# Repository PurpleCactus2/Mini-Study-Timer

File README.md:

# Mini-Study-Timer
A small and portable study timer for keeping track of the time you spend learning or working on projects!

## Introduction
This is a mini study timer meant to track the time that you have spent studying. Its features include:

- A 0.91" OLED display to display the timer
- Buttons to control start/stop/pause/reset
- Visual indicator LEDs
- Planned functionality with a rotary encoder to set time

## PCB
My aim with the PCB was to make it relatively compact so that you could easily fit it into a backpack or pocket. But at the same time I also wanted to make it easy to work with since I am quite inexperienced with soldering and assembly.

### Schematic
The schematic itself follows a pretty regular layout.

Here is the XIAO ESP32 C3 as the main microcontroller:
<br>

The battery will connect to the battery pads on the bottom of the Xiao (*see PCB*)<br><br>

Here is the 0.91" OLED:
<br><br>

I have included some extra pullup resistors and decoupling capacitors as recommended by the guide.<br><br>

This is the rotary encoder:
<br><br>

I have included a very basic filter to hopefully help with debouncing.<br><br>

Here are the rest of the components:
<br>

These are the basic switches, LEDs and extra I2C headers that I have included along with a JST-PH connector for the battery.<br><br>

### PCB
As I said before, I have tried compacting the PCB layout quite a bit:
<br>

But I have also tried to arrange the parts in a way that makes sense, with the buttons and encoder below the screen and with the power switch on the right.<br><br>

Here are those battery pads I was talking about within the footprint of the Xiao:
<br><br>

To connect these pads to the PCB I will simply push a header pin through the hole from the other side and solder it that way.

## Code
At its core the code runs a basic timer with the buttons controlling its main functions.
Here is a table showing the controls and functions of the timer:

| Component | Function |
|---|---|
| SW1 (Left on PCB) | Starts/pauses timer |
| SW2 (Right on PCB) | Resets and stops the timer |
| Rotary Encoder (UNFINISHED FEATURE) | Sets a countdown timer |
| Red LED | Lights up when timer is stopped |
| Green LED | Lights up when timer is active |

Unfortunately I was unable to completely finish the code for the rotary encoder in time, so right now the device can only count up the minutes and hours you have spent working.

[Here](https://wokwi.com/projects/479273044321545217) is the simulation i've made on WokWi to test the current functions (Note: I have absolutely no idea why, but the green LED connected to D6 on the XIAO ESP32 C3 simply refuses to turn on)

## BOM
|Item                    |Qty|Supplier  |Cost/item|Total Cost|link                                                                                                                                                                                                                                                                                                                                                                                                                                                                                                                                                                                                                                                                                                                                                                                    |
|------------------------|---|----------|---------|----------|----------------------------------------------------------------------------------------------------------------------------------------------------------------------------------------------------------------------------------------------------------------------------------------------------------------------------------------------------------------------------------------------------------------------------------------------------------------------------------------------------------------------------------------------------------------------------------------------------------------------------------------------------------------------------------------------------------------------------------------------------------------------------------------|
|XIAO ESP32 C3           |1  |AliExpress|$8.55    |$8.55     |[AliExpress](https://www.aliexpress.com/item/1005008791937363.html?spm=a2g0o.productlist.main.2.3fccf128mRG5wj&algo_pvid=f91a3f44-7054-4a6c-b5ca-71a791d5faf8&algo_exp_id=f91a3f44-7054-4a6c-b5ca-71a791d5faf8-1&pdp_ext_f=%7B%22order%22%3A%221602%22%2C%22eval%22%3A%221%22%2C%22fromPage%22%3A%22search%22%7D&pdp_npi=6%40dis%21NOK%2179.84%2111.94%21%21%218.33%211.25%21%400b5e1a3817935633084165522e0e0a%2112000052930246748%21sea%21NO%218463637778%21X%211%210%21n_tag%3A-29911%3Bd%3A22d43e35%3Bm03_new_user%3A-29895%3BpisId%3A5000000219877342&curPageLogUid=niJ9W14AGW5V&utparam-url=scene%3Asearch%7Cquery_from%3A%7Cx_object_id%3A1005008791937363%7C_p_origin_prod%3A)                                                                                                                 |
|0.91" OLED              |1  |AliExpress|$2.43    |$2.43     |[AliExpress](https://www.aliexpress.com/item/1005006823025817.html?spm=a2g0o.productlist.main.4.468b411fr6AAZN&algo_pvid=2569d209-d20a-4ce9-8cd6-a8dd480e45cc&aem_p4p_detail=20261101120438123246892630680005280555&algo_exp_id=2569d209-d20a-4ce9-8cd6-a8dd480e45cc-3&pdp_ext_f=%7B%22order%22%3A%22598%22%2C%22eval%22%3A%221%22%2C%22fromPage%22%3A%22search%22%7D&pdp_npi=6%40dis%21NOK%2122.67%2120.23%21%21%2115.69%2114.00%21%40210382de17935634779592233e10aa%2112000038417220460%21sea%21NO%218463637778%21X%211%210%21n_tag%3A-29911%3Bd%3A22d43e35%3Bm03_new_user%3A-29895%3BpisId%3A5000000220744683&curPageLogUid=QDjpxSoLt2EF&utparam-url=scene%3Asearch%7Cquery_from%3A%7Cx_object_id%3A1005006823025817%7C_p_origin_prod%3A&search_p4p_id=20261101120438123246892630680005280555_1)   |
|Rotary Encoder          |1  |AliExpress|$1.56    |$1.56     |[AliExpress](https://www.aliexpress.com/item/1005007644083514.html?spm=a2g0o.productlist.main.1.363968b6NvMQQN&algo_pvid=ecab3b09-9889-40fe-b5bb-468045627bf3&algo_exp_id=ecab3b09-9889-40fe-b5bb-468045627bf3-0&pdp_ext_f=%7B%22order%22%3A%224885%22%2C%22spu_best_type%22%3A%22price%22%2C%22eval%22%3A%221%22%2C%22fromPage%22%3A%22search%22%7D&pdp_npi=6%40dis%21NOK%2114.57%2110.45%21%21%211.52%211.10%21%400b88ab6717935636427541071e0f7b%2112000041630839409%21sea%21NO%218463637778%21X%211%210%21n_tag%3A-29911%3Bd%3A22d43e35%3Bm03_new_user%3A-29895%3BpisId%3A5000000219877342&curPageLogUid=OE90QjaOwzU0&utparam-url=scene%3Asearch%7Cquery_from%3A%7Cx_object_id%3A1005007644083514%7C_p_origin_prod%3A)                                                                             |
|Passive Components      |1  |AliExpress|$8.92    |$8.92     |[Capacitors](https://www.aliexpress.com/item/1005011747293156.html?spm=a2g0o.productlist.main.4.71c07baeewHVSt&algo_pvid=53fa7523-91ab-4fc5-9a37-791a7be0863d&aem_p4p_detail=202611011216112607374392124900005273353&algo_exp_id=53fa7523-91ab-4fc5-9a37-791a7be0863d-3&pdp_ext_f=%7B%22order%22%3A%223213%22%2C%22eval%22%3A%221%22%2C%22fromPage%22%3A%22search%22%7D&pdp_npi=6%40dis%21NOK%2122.06%2118.62%21%21%2115.27%2112.89%21%4021613ab217935641713446056e0fa2%2112000056423315138%21sea%21NO%218463637778%21X%211%210%21n_tag%3A-29911%3Bd%3A22d43e35%3Bm03_new_user%3A-29895%3BpisId%3A5000000221000707&curPageLogUid=9U2JRaZ3bgVG&utparam-url=scene%3Asearch%7Cquery_from%3A%7Cx_object_id%3A1005011747293156%7C_p_origin_prod%3A&search_p4p_id=202611011216112607374392124900005273353_3) [Resistors](https://www.aliexpress.com/item/1005002994755806.html?spm=a2g0o.cart.0.0.3f3a38dakuPmuS&mp=1&pdp_npi=6%40dis%21NOK%21NOK+29.90%21NOK+24.36%21%21NOK+24.36%21%21%21%400b8848e317935654396147496e0f29%2112000023122336560%21ct%21NO%218463637778%21%211%210%21)|
|JST-PH Connector        |1  |AliExpress|$1.67    |$1.67     |[AliExpress](https://www.aliexpress.com/item/1005004955655144.html?spm=a2g0o.productlist.main.33.673e3206X0j96K&algo_pvid=20e9831a-0538-42f5-89b6-7565b2dfc96a&algo_exp_id=20e9831a-0538-42f5-89b6-7565b2dfc96a-32&pdp_ext_f=%7B%22order%22%3A%223896%22%2C%22spu_best_type%22%3A%22price%22%2C%22eval%22%3A%221%22%2C%22fromPage%22%3A%22search%22%7D&pdp_npi=6%40dis%21NOK%218.34%216.96%21%21%210.87%210.73%21%400b88ab8a17935646038367827e104c%2112000033370425480%21sea%21NO%218463637778%21X%211%210%21n_tag%3A-29911%3Bd%3A22d43e35%3Bm03_new_user%3A-29895%3BpisId%3A5000000220732436&curPageLogUid=yGrFZekc6acZ&utparam-url=scene%3Asearch%7Cquery_from%3A%7Cx_object_id%3A1005004955655144%7C_p_origin_prod%3A)                                                                             |
|PCB                     |1  |JLCPCB    |$6.72    |$6.72     |[JLCPCB](https://cart.jlcpcb.com/quote?spm=jlcpcb.Public.2006&spm=Jlcpcb.Instantquote&spm=Jlcpcb.Instantquote&_t=1791669462672&_t=1793564789078&up_spm=Jlcpcb.Loginpage.1003&up_spm=Jlcpcb.Loginpage.1003)                                                                                                                                                                                                                                                                                                                                                                                                                                                                                                                                                                                        |
|3.7V LiPo               |1  |AliExpress|$4.11    |$4.11     |[AliExpress](https://www.aliexpress.com/item/1005010132479554.html?spm=a2g0o.productlist.main.1.401e5072TdpAZM&algo_pvid=f599faf2-6e03-4dbc-bcfc-387a4df46eb1&algo_exp_id=f599faf2-6e03-4dbc-bcfc-387a4df46eb1-0&pdp_ext_f=%7B%22order%22%3A%221236%22%2C%22spu_best_type%22%3A%22price%22%2C%22eval%22%3A%221%22%2C%22fromPage%22%3A%22search%22%7D&pdp_npi=6%40dis%21NOK%21217.91%2138.38%21%21%21150.81%2126.56%21%4021038b2f17935651508853358e0d64%2112000051255130084%21sea%21NO%218463637778%21X%211%210%21n_tag%3A-29911%3Bd%3A22d43e35%3Bm03_new_user%3A-29895%3BpisId%3A5000000219877342&curPageLogUid=Mbz1Z1oNIHlF&utparam-url=scene%3Asearch%7Cquery_from%3A%7Cx_object_id%3A1005010132479554%7C_p_origin_prod%3A)                                                                         |
|Estimated total shipping|1  |          |         |$5.86     |                                                                                                                                                                                                                                                                                                                                                                                                                                                                                                                                                                                                                                                                                                                                                                                        |

- The prices listed here represent the **maximum possible** prices for each of the items, in reality, significant discounts do apply
- I am completely willing to cover all additional costs that are not coverered by the base 30$

Cart Screenshots (1kr ≈ $0.1):

Aliexpress order:

Total (discounts at time checked + shipping/tax): **$29.22** <br> <br>

JLCPCB order:

Total (with discounts at time checked + shipping/tax): **$6.72**

Grand Total: **$35.94**

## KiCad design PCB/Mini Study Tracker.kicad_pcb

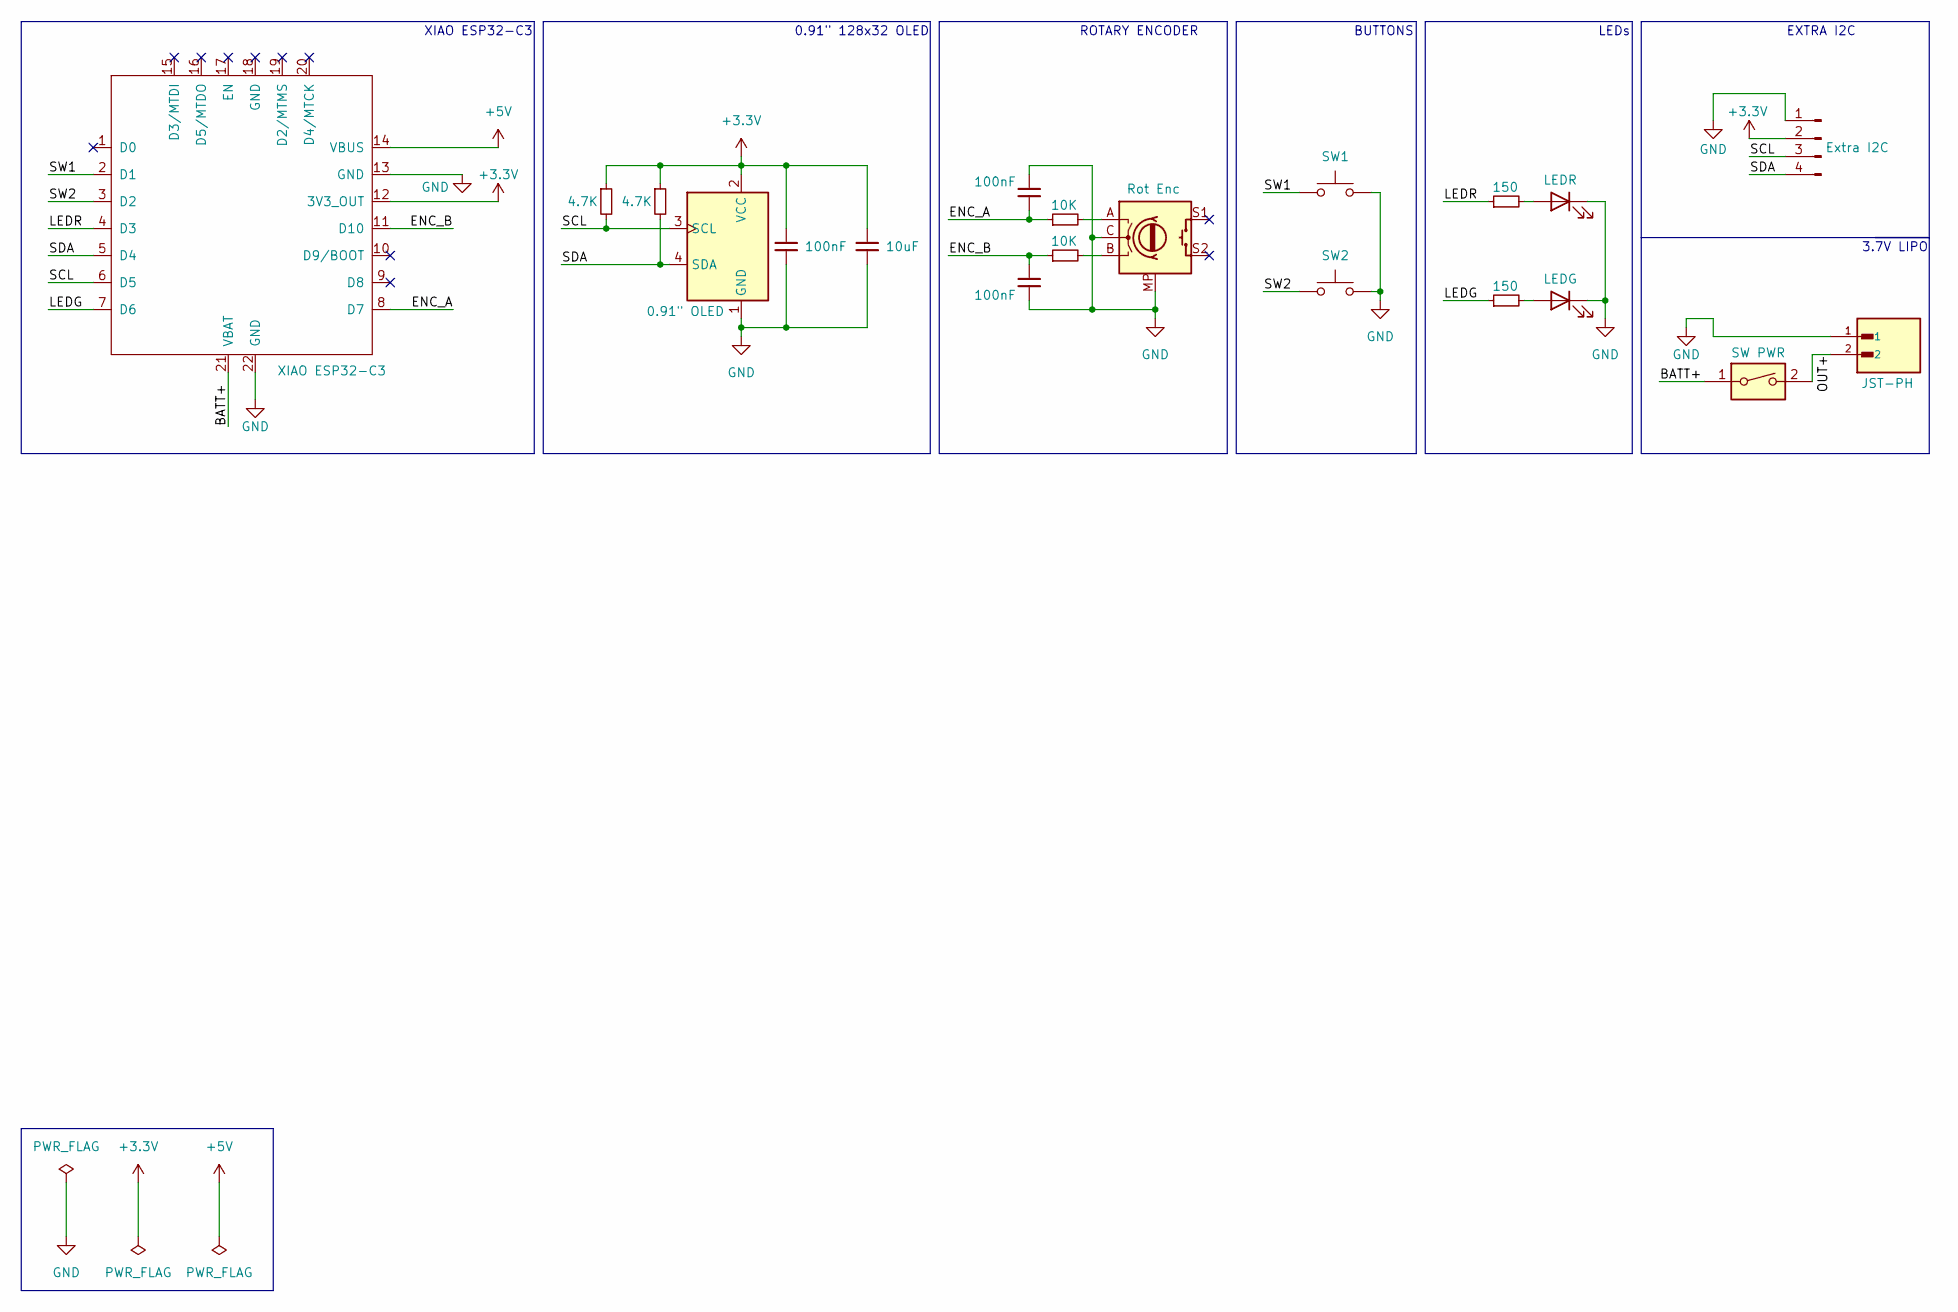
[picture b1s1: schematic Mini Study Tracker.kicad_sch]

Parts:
C1, C3, C4: 100nF; C_Disc_D4.7mm_W2.5mm_P5.00mm
C2: 10uF; C_Disc_D4.7mm_W2.5mm_P5.00mm
D1: LEDR; LED_D5.0mm
D2: LEDG; LED_D5.0mm
ENC1: Rot Enc; RotaryEncoder_Alps_EC11E-Switch_Vertical_H20mm
J2: Extra I2C; PinHeader_1x04_P2.54mm_Vertical
J3: JST-PH; JST-PH DIP; PARTREV R0
R1, R2: 4.7K; R_Axial_DIN0207_L6.3mm_D2.5mm_P7.62mm_Horizontal
R3, R4: 150; R_Axial_DIN0207_L6.3mm_D2.5mm_P7.62mm_Horizontal
R5, R6: 10K; R_Axial_DIN0207_L6.3mm_D2.5mm_P7.62mm_Horizontal
SW1: SW1; SW_PUSH_6mm_H4.3mm
SW2: SW2; SW_PUSH_6mm_H4.3mm
SW3: SW PWR; KCD11_15x10mm_SW
U1: XIAO ESP32-C3; XIAO-ESP32-C3-DIP-SMD
U2: 0.91" OLED; OLED_0.91_128x32

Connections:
+3.3V: C1.1, C2.1, J2.2, R1.1, R2.1, U1.12 (3V3_OUT), U2.2 (VCC)
+5V: U1.14 (VBUS)
/BATT+: SW3.1, U1.21 (VBAT)
/ENC_A: C4.2, R5.1, U1.8 (D7)
/ENC_B: C3.1, R6.1, U1.11 (D10)
/LEDG: R4.1, U1.7 (D6)
/LEDR: R3.1, U1.4 (D3)
/OUT+: J3.2, SW3.2
/SCL: J2.3, R1.2, U1.6 (D5), U2.3 (SCL)
/SDA: J2.4, R2.2, U1.5 (D4), U2.4 (SDA)
/SW1: SW1.1, U1.2 (D1)
/SW2: SW2.1, U1.3 (D2)
GND: C1.2, C2.2, C3.2, C4.1, D1.1 (K), D2.1 (K), ENC1.C, ENC1.MP, J2.1, J3.1, SW1.2, SW2.2, U1.13 (GND), U1.22 (GND), U2.1 (GND)
unnamed: D1.2 (A), R3.2
unnamed: D2.2 (A), R4.2
unnamed: ENC1.A, R5.2
unnamed: ENC1.B, R6.2

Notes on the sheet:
ROTARY ENCODER
BUTTONS
LEDs
0.91" 128x32 OLED
EXTRA I2C
XIAO ESP32-C3
3.7V LIPO

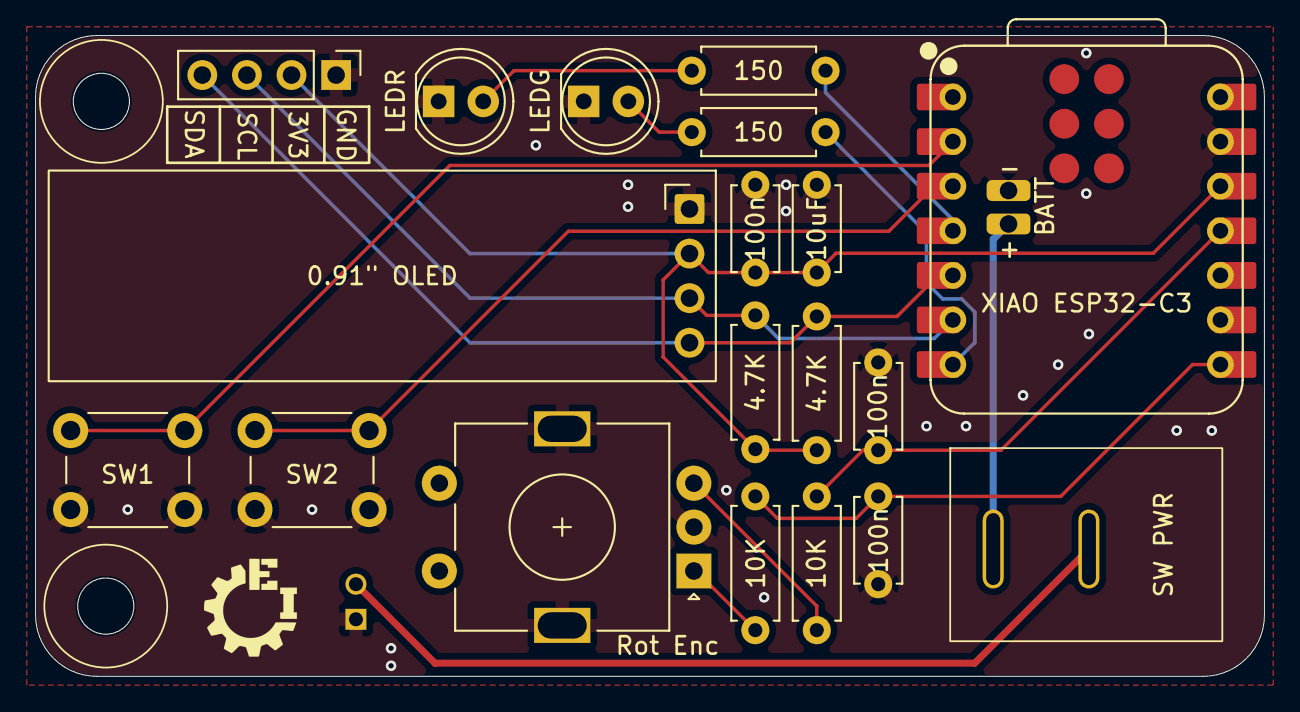
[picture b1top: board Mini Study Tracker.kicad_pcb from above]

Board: 2 copper layers, 70.0 x 36.5 mm, 20 parts (1 on the bottom side), 16 nets.

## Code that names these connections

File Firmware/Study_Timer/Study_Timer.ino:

#include <Wire.h>
#include <Adafruit_GFX.h>
#include <Adafruit_SSD1306.h>
#include <Fonts/Org_01.h>
#include <SimpleEncoder.h>
#include <Timer.h>

//OLED setup
const int ScreenWidth = 128;
const int ScreenHeight = 32;
Adafruit_SSD1306 display(ScreenWidth, ScreenHeight, &Wire, -1);

//Button setup
const int SW1 = 3;
const int SW2 = 4;

//Rotary encoder setup
const int ENC_A = 20;
const int ENC_B = 10;
const int ButtonPin = 8;
long DialValue;
long MinDial = 0;
long MaxDial = 99;
SimpleEncoder encoder(ButtonPin, ENC_A, ENC_B, DialValue, MinDial, MaxDial, 1);

//LED setup
const int LEDR = 5;
const int LEDG = 21;

//Logic Setup
bool TimerActive = false;
bool TimerPaused = false;
bool SW1State = false;
bool SW2State = false;
bool SW1PrevState = true;
bool SW2PrevState = true;
long SetMinutes = 0;
long SetHours = 0;
unsigned long SW1LastDebounceTime = 0;
unsigned long SW1DebounceDelay = 200;
unsigned long SW2LastDebounceTime = 0;
unsigned long SW2DebounceDelay = 200;
unsigned long TimerMinutes = 0;
unsigned long TimerHours = 0;
unsigned long TimerSeconds = 0;
unsigned long PrevSeconds = 0;
Timer Timer;

//Config
bool DoTitle = true;
bool ShowSeconds = true;

void setup() {
  Serial.begin(9600);

  pinMode(SW1, INPUT_PULLUP);
  pinMode(SW2, INPUT_PULLUP);

  pinMode(LEDR, OUTPUT);
  pinMode(LEDG, OUTPUT);

  pinMode(ENC_A, INPUT_PULLUP);
  pinMode(ENC_B, INPUT_PULLUP);

  if (!display.begin(SSD1306_SWITCHCAPVCC, 0x3C)) {
    Serial.println("Screen not found");
    while (true) {
    }
  }

  Serial.println("Screen started succesfully");

  if (DoTitle == true) {
    display.clearDisplay();
    //Title
    display.setTextColor(1);
    display.setTextWrap(false);
    display.setCursor(2, 2);
    display.print("Mini Study Timer");
    //Name
    display.setFont(&Org_01);
    display.setCursor(2, 29);
    display.print("Balint Koch");
    display.display();
    delay(1000);
  }
  
  drawTimer(0, 0, 0);
  digitalWrite(LEDR, HIGH);
}

void loop() {

  SW1State = digitalRead(SW1);
  SW2State = digitalRead(SW2);

  if (SW1State == LOW && SW1PrevState == HIGH) {
    if ((millis() - SW1LastDebounceTime) > SW1DebounceDelay) {

      if (!TimerActive && !TimerPaused) {

      Serial.println("Timer Started");
      digitalWrite(LEDR, LOW);
      digitalWrite(LEDG, HIGH);
      TimerActive = true;
      Timer.start();

    } else if (TimerActive) {

      Timer.pause();
      TimerActive = false;
      TimerPaused = true;
      digitalWrite(LEDR, HIGH);
      digitalWrite(LEDG, LOW);
      Serial.println("Timer paused");

    } else if (TimerPaused) {

      Timer.resume();
      TimerPaused = false;
      TimerActive = true;
      digitalWrite(LEDR, LOW);
      digitalWrite(LEDG, HIGH);
      Serial.println("Timer resumed");
    }
    SW1LastDebounceTime = millis();
    }
  }
  SW1PrevState = SW1State;
  
  if (SW2State == LOW && SW2PrevState == HIGH) {
    if ((millis() - SW2LastDebounceTime) > SW2DebounceDelay) {

      if (TimerActive || TimerPaused) {
        Timer.stop();
        TimerPaused = false;
        TimerActive = false;
        drawTimer(0, 0, 0);
        digitalWrite(LEDR, HIGH);
        digitalWrite(LEDG, LOW);
        Serial.println("Timer Reset");
      }
      SW2LastDebounceTime = millis();
    }
  }
  SW2PrevState = SW2State;

  if (TimerActive) { 

    TimerSeconds = (Timer.read() / 1000) % 60;
    TimerMinutes = (Timer.read() / 60000) % 60;
    TimerHours = Timer.read() / 3600000;
  }

  
  if (TimerSeconds != PrevSeconds) {

    PrevSeconds = TimerSeconds;
    drawTimer(TimerHours, TimerMinutes, TimerSeconds);
    Serial.print("Current seconds: ");
    Serial.println(TimerSeconds);
  }
}

void drawTimer(unsigned long Hours, unsigned long Minutes, unsigned long Seconds) {
  display.clearDisplay();
  // Hours
  display.setTextColor(1);
  display.setTextSize(2);
  display.setTextWrap(false);
  display.setCursor(37, 9);
  display.print(Hours);
  // Minutes
  display.setCursor(69, 9);
  display.print(Minutes);
  // ":"
  display.setCursor(59, 9);
  display.print(":");
   // Seconds
  if (ShowSeconds) {
   display.setTextSize(1);
   display.setCursor(93, 16);
   display.print(Seconds);
  }
  display.display();
}
